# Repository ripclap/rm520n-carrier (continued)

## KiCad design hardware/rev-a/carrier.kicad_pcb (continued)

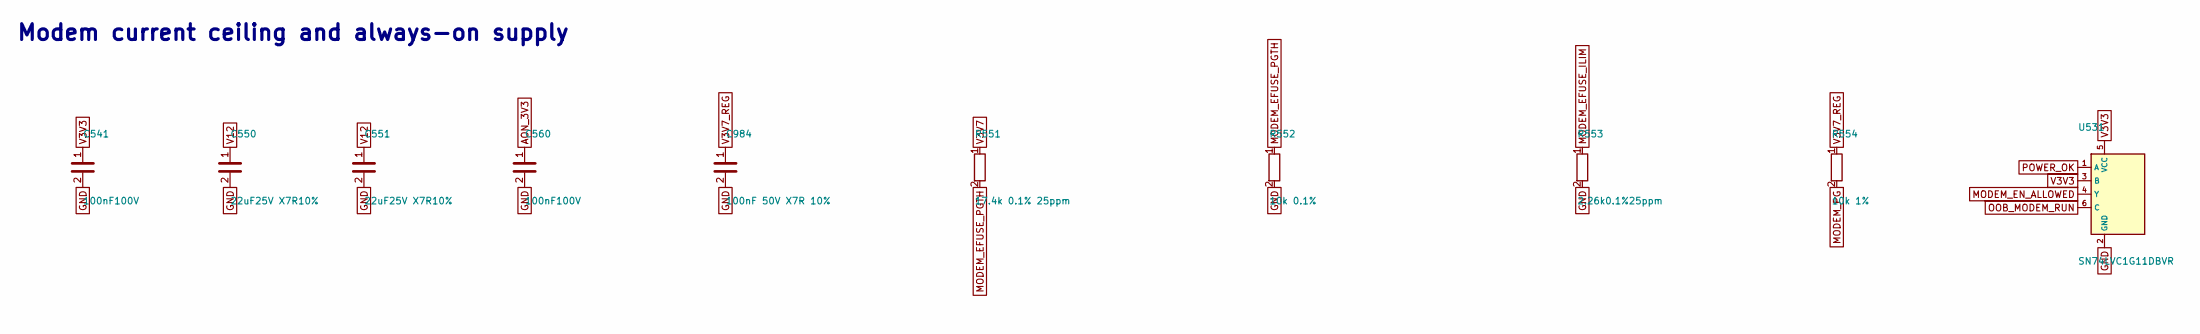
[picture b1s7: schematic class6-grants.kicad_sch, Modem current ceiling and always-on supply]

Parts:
C541, C560: 100nF100V; C_0603_1608Metric; MPN GRM188R72A104KA35D
C550, C551: 22uF25V X7R10%; C_1210_3225Metric; MPN CL32B226KAJNNNE; LCSC C309062
C984: 100nF 50V X7R 10%; C_0402_1005Metric; MPN CL05B104KB5NNNC; LCSC C960916
R551: 17.4k 0.1% 25ppm; R_0402_1005Metric; MPN RT0402BRD0717K4L
R552: 10k 0.1%; R_0402_1005Metric; MPN TNPW040210K0BEED
R553: 2.26k0.1%25ppm; R_0603_1608Metric; MPN RT0603BRD072K26L
R554: 10k 1%; R_0603_1608Metric; MPN RC0603FR-0710KL
U531: SN74LVC1G11DBVR; SOT-23-6; MPN SN74LVC1G11DBVR

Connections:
AON_3V3: C560.1; also elsewhere on the board
GND: C541.2, C550.2, C551.2, C560.2, C984.2, R552.2, R553.2, U531.2 (GND); also elsewhere on the board
MODEM_EFUSE_ILIM: R553.1; also elsewhere on the board
MODEM_EFUSE_PGTH: R551.2, R552.1; also elsewhere on the board
MODEM_EN_ALLOWED: U531.4 (Y); also elsewhere on the board
MODEM_PG: R554.2; also elsewhere on the board
OOB_MODEM_RUN: U531.6 (C); also elsewhere on the board
POWER_OK: U531.1 (A); also elsewhere on the board
V3V3: C541.1, U531.3 (B), U531.5 (VCC); also elsewhere on the board
V3V7: R551.1; also elsewhere on the board
V3V7_REG: C984.1, R554.1; also elsewhere on the board
V12: C550.1, C551.1; also elsewhere on the board

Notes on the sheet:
Modem current ceiling and always-on supply

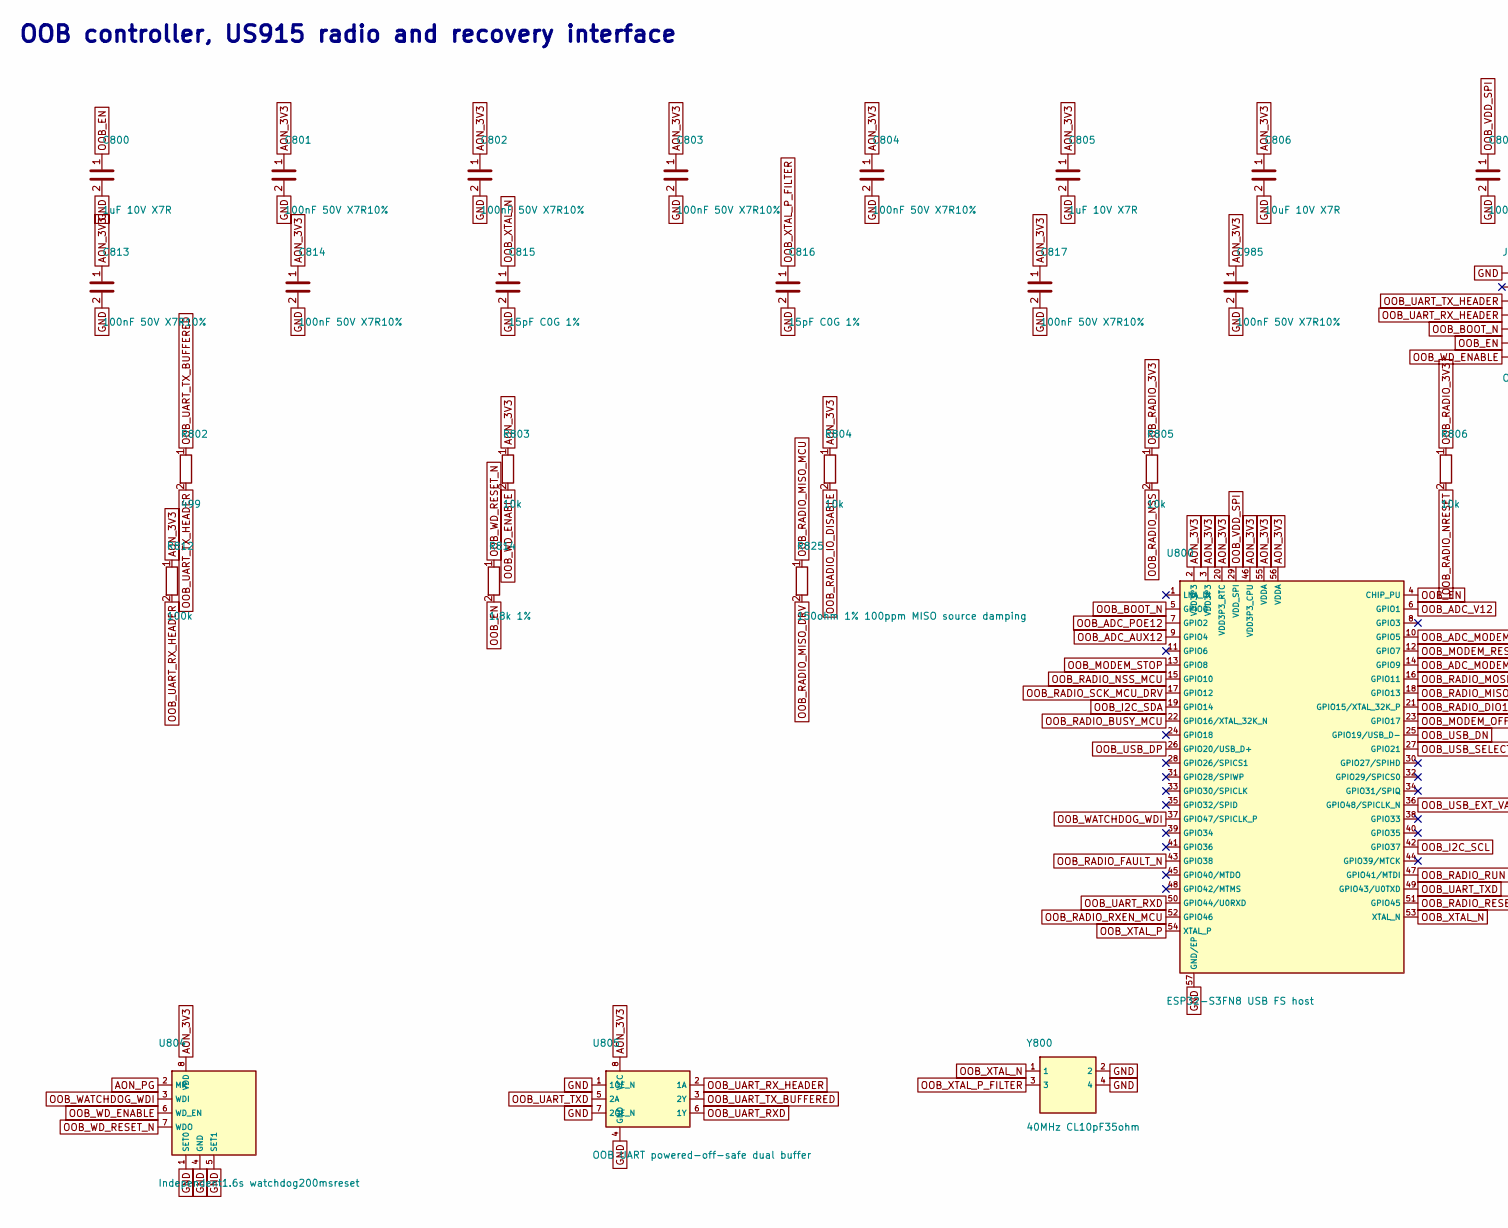
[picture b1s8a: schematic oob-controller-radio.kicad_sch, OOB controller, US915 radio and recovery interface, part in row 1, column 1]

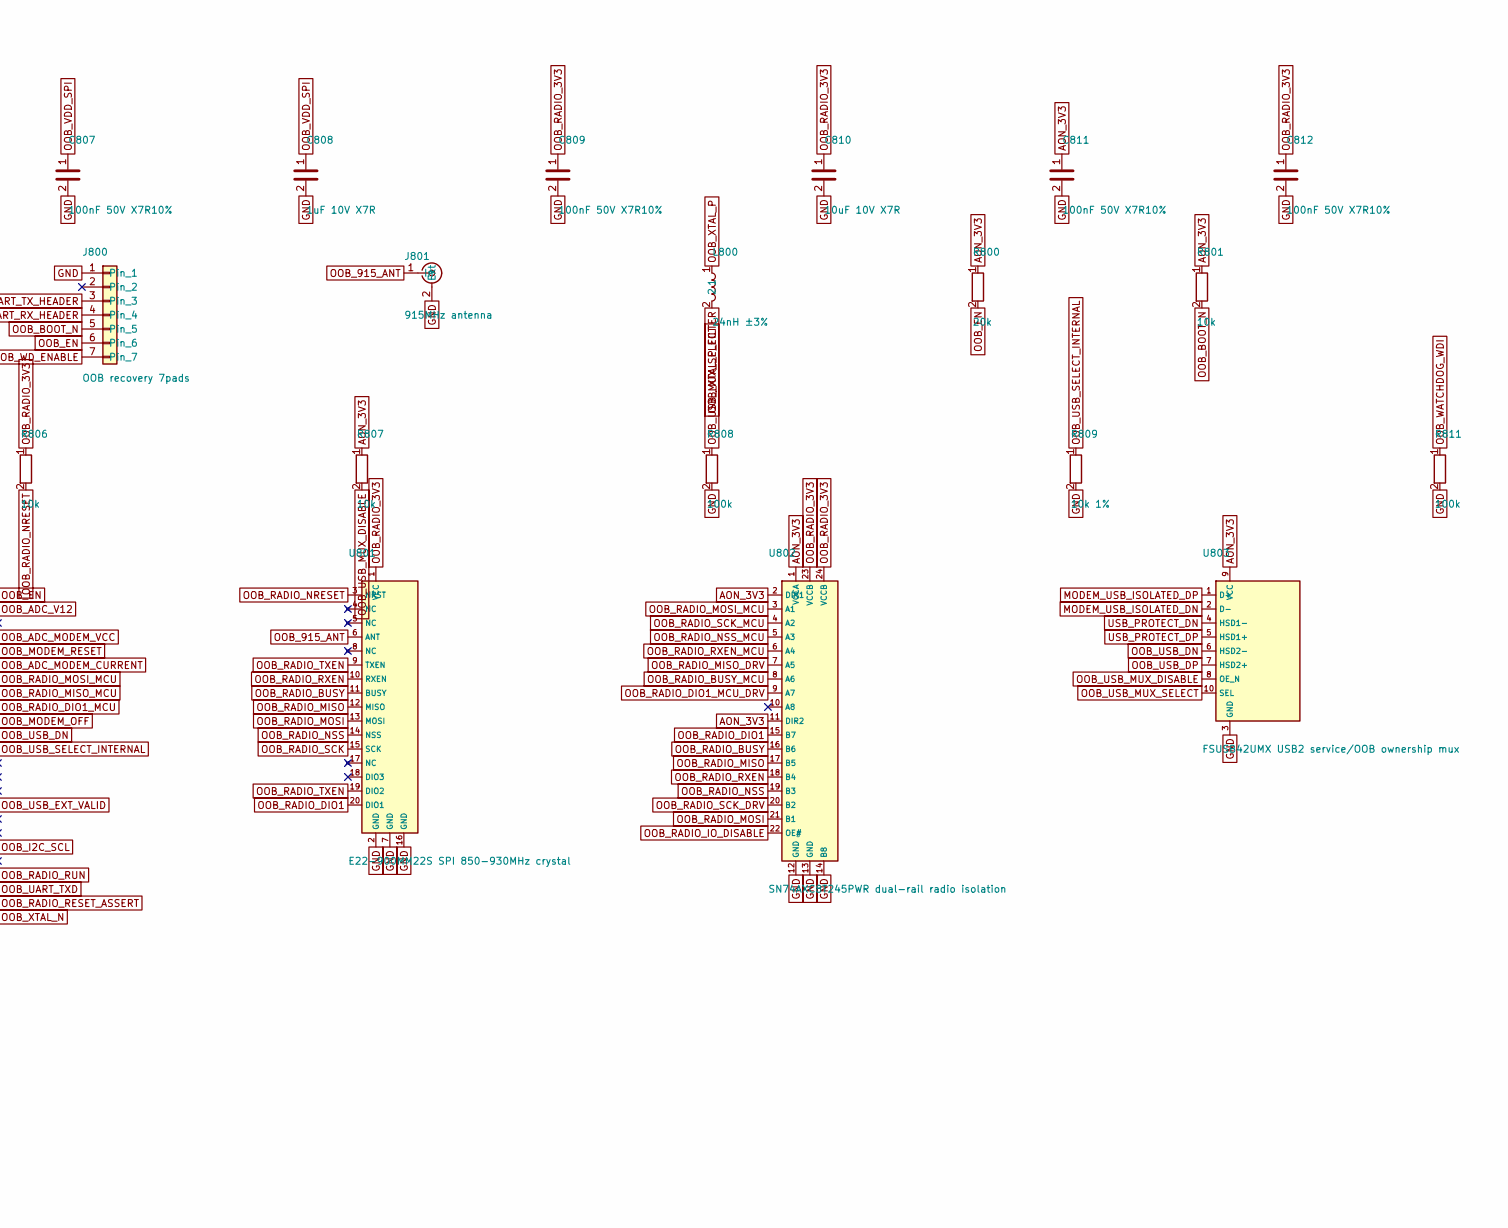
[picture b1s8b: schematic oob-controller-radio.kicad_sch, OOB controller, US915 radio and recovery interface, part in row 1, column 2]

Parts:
C800, C805, C808: 1uF 10V X7R; C_0603_1608Metric; MPN 885012206026
C801, C802, C803, C804, C807, C811, C812, C813, C814, C817, C985: 100nF 50V X7R10%; C_0402_1005Metric; MPN CL05B104KB5NNNC; LCSC C960916
C806, C810: 10uF 10V X7R; C_0805_2012Metric; MPN 885012207026
C809: 100nF 50V X7R10%; C_0402_1005Metric_DenseRevA_C809; MPN CL05B104KB5NNNC; LCSC C960916
C815, C816: 15pF C0G 1%; C_0402_1005Metric; MPN KGM05ACG1H150FH
J800: OOB recovery 7pads; OOB_SERVICE_7PAD; MPN PCB service pads
J801: 915MHz antenna; UFL_HIROSE_DenseRevA_J801; MPN U.FL-R-SMT-1(80)
L800: 24nH ±3%; Murata_LQW15AN_0402_Manufacturer_DenseRevA_L800; MPN LQW15AN24NH00D
R800: 20k; R_0402_1005Metric; MPN CRCW040220K0FKED
R801, R803, R804, R805, R806, R807: 10k; R_0402_1005Metric; MPN CRCW040210K0FKED
R802: 499; R_0402_1005Metric; MPN CRCW0402499RFKED
R808, R811, R812: 100k; R_0402_1005Metric; MPN CRCW0402100KFKED
R809: 10k 1%; R_0402_1005Metric; MPN CRCW040210K0FKED
R814: 1.8k 1%; R_0402_1005Metric; MPN RC0402FR-071K8L; LCSC C163481
R825: 150ohm 1% 100ppm MISO source damping; R_0402_1005Metric; MPN CRCW0402150RFKED
U800: ESP32-S3FN8 USB FS host; ESP32_S3FN8_QFN56; MPN ESP32-S3FN8
U801: E22-900MM22S SPI 850-930MHz crystal; Ebyte_E22_900MM22S_10x10_20Pad_DenseRevA_U801; MPN E22-900MM22S; LCSC C5333985
U802: SN74AXC8T245PWR dual-rail radio isolation; RevA_DensePrimary100_PIN50_Flash_U802; MPN SN74AXC8T245PWR; LCSC C882718
U803: FSUSB42UMX USB2 service/OOB ownership mux; FSUSB42_UQFN10_1p4x1p8; MPN FSUSB42UMX; LCSC C11145
U804: Independent1.6s watchdog200msreset; TI_DDF8_TPS3435; MPN TPS3435CAKAGDDFR; LCSC C6339182
U805: OOB UART powered-off-safe dual buffer; TI_DCU8_LVC2G125; MPN SN74LVC2G125DCUR
Y800: 40MHz CL10pF35ohm; Abracon_ABM8_3225_DenseRevA_Y800; MPN ABM8-40.000MHZ-10-D1G-T; LCSC C1986736

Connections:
AON_3V3: C801.1, C802.1, C803.1, C804.1, C805.1, C806.1, C811.1, C813.1, C814.1, C817.1, C985.1, R800.1, R801.1, R803.1, R804.1, R807.1, R812.1, U800.2 (VDD3P3), U800.3 (VDD3P3), U800.20 (VDD3P3_RTC), U800.46 (VDD3P3_CPU), U800.55 (VDDA), U800.56 (VDDA), U802.1 (VCCA), U802.2 (DIR1), U802.11 (DIR2), U803.9 (VCC), U804.8 (VDD), U805.8 (VCC); also elsewhere on the board
AON_PG: U804.2 (MR); also elsewhere on the board
GND: C800.2, C801.2, C802.2, C803.2, C804.2, C805.2, C806.2, C807.2, C808.2, C809.2, C810.2, C811.2, C812.2, C813.2, C814.2, C815.2, C816.2, C817.2, C985.2, J800.1, J801.2 (Ext), R808.2, R809.2, R811.2, U800.57 (GND/EP), U801.2 (GND), U801.7 (GND), U801.16 (GND), U802.12 (GND), U802.13 (GND), U802.14 (B8), U803.3 (GND), U804.1 (SET0), U804.4 (GND), U804.5 (SET1), U805.1 (1OE_N), U805.4 (GND), U805.7 (2OE_N), Y800.2, Y800.4; also elsewhere on the board
MODEM_USB_ISOLATED_DN: U803.2 (D-); also elsewhere on the board
MODEM_USB_ISOLATED_DP: U803.1 (D+); also elsewhere on the board
OOB_915_ANT: J801.1 (In), U801.6 (ANT)
OOB_ADC_AUX12: U800.9 (GPIO4); also elsewhere on the board
OOB_ADC_MODEM_CURRENT: U800.14 (GPIO9); also elsewhere on the board
OOB_ADC_MODEM_VCC: U800.10 (GPIO5); also elsewhere on the board
OOB_ADC_POE12: U800.7 (GPIO2); also elsewhere on the board
OOB_ADC_V12: U800.6 (GPIO1); also elsewhere on the board
OOB_BOOT_N: J800.5, R801.2, U800.5 (GPIO0)
OOB_EN: C800.1, J800.6, R800.2, R814.2, U800.4 (CHIP_PU); also elsewhere on the board
OOB_I2C_SCL: U800.42 (GPIO37); also elsewhere on the board
OOB_I2C_SDA: U800.19 (GPIO14); also elsewhere on the board
OOB_MODEM_OFF: U800.23 (GPIO17); also elsewhere on the board
OOB_MODEM_RESET: U800.12 (GPIO7); also elsewhere on the board
OOB_MODEM_STOP: U800.13 (GPIO8); also elsewhere on the board
OOB_RADIO_3V3: C809.1, C810.1, C812.1, R805.1, R806.1, U801.1 (VCC), U802.23 (VCCB), U802.24 (VCCB); also elsewhere on the board
OOB_RADIO_BUSY: U801.11 (BUSY), U802.16 (B6)
OOB_RADIO_BUSY_MCU: U800.22 (GPIO16/XTAL_32K_N), U802.8 (A6)
OOB_RADIO_DIO1: U801.20 (DIO1), U802.15 (B7)
OOB_RADIO_DIO1_MCU: U800.21 (GPIO15/XTAL_32K_P); also elsewhere on the board
OOB_RADIO_DIO1_MCU_DRV: U802.9 (A7); also elsewhere on the board
OOB_RADIO_FAULT_N: U800.43 (GPIO38); also elsewhere on the board
OOB_RADIO_IO_DISABLE: R804.2, U802.22 (OE#); also elsewhere on the board
OOB_RADIO_MISO: U801.12 (MISO), U802.17 (B5)
OOB_RADIO_MISO_DRV: R825.2, U802.7 (A5)
OOB_RADIO_MISO_MCU: R825.1, U800.18 (GPIO13)
OOB_RADIO_MOSI: U801.13 (MOSI), U802.21 (B1)
OOB_RADIO_MOSI_MCU: U800.16 (GPIO11), U802.3 (A1)
OOB_RADIO_NRESET: R806.2, U801.3 (NRST); also elsewhere on the board
OOB_RADIO_NSS: R805.2, U801.14 (NSS), U802.19 (B3)
OOB_RADIO_NSS_MCU: U800.15 (GPIO10), U802.5 (A3)
OOB_RADIO_RESET_ASSERT: U800.51 (GPIO45); also elsewhere on the board
OOB_RADIO_RUN: U800.47 (GPIO41/MTDI); also elsewhere on the board
OOB_RADIO_RXEN: U801.10 (RXEN), U802.18 (B4)
OOB_RADIO_RXEN_MCU: U800.52 (GPIO46), U802.6 (A4); also elsewhere on the board
OOB_RADIO_SCK: U801.15 (SCK); also elsewhere on the board
OOB_RADIO_SCK_DRV: U802.20 (B2); also elsewhere on the board
OOB_RADIO_SCK_MCU: U802.4 (A2); also elsewhere on the board
OOB_RADIO_SCK_MCU_DRV: U800.17 (GPIO12); also elsewhere on the board
OOB_RADIO_TXEN: U801.9 (TXEN), U801.19 (DIO2)
OOB_UART_RXD: U800.50 (GPIO44/U0RXD), U805.6 (1Y)
OOB_UART_RX_HEADER: J800.4, R812.2, U805.2 (1A)
OOB_UART_TXD: U800.49 (GPIO43/U0TXD), U805.5 (2A)
OOB_UART_TX_BUFFERED: R802.1, U805.3 (2Y)
OOB_UART_TX_HEADER: J800.3, R802.2
OOB_USB_DN: U800.25 (GPIO19/USB_D-), U803.6 (HSD2-)
OOB_USB_DP: U800.26 (GPIO20/USB_D+), U803.7 (HSD2+)
OOB_USB_EXT_VALID: U800.36 (GPIO48/SPICLK_N); also elsewhere on the board
OOB_USB_MUX_DISABLE: R807.2, U803.8 (OE_N); also elsewhere on the board
OOB_USB_MUX_SELECT: R808.1, U803.10 (SEL); also elsewhere on the board
OOB_USB_SELECT_INTERNAL: R809.1, U800.27 (GPIO21); also elsewhere on the board
OOB_VDD_SPI: C807.1, C808.1, U800.29 (VDD_SPI)
OOB_WATCHDOG_WDI: R811.1, U800.37 (GPIO47/SPICLK_P), U804.3 (WDI)
OOB_WD_ENABLE: J800.7, R803.2, U804.6 (WD_EN)
OOB_WD_RESET_N: R814.1, U804.7 (WDO)
OOB_XTAL_N: C815.1, U800.53 (XTAL_N), Y800.1
OOB_XTAL_P: L800.1, U800.54 (XTAL_P)
OOB_XTAL_P_FILTER: C816.1, L800.2, Y800.3
USB_PROTECT_DN: U803.4 (HSD1-); also elsewhere on the board
USB_PROTECT_DP: U803.5 (HSD1+); also elsewhere on the board

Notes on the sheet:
OOB controller, US915 radio and recovery interface

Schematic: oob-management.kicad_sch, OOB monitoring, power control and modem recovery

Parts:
C552: 100nF50V X7R10%; C_0402_1005Metric; MPN CL05B104KB5NNNC; LCSC C960916
C553, C554, C555, C561: 22uF25V X7R10%; C_1210_3225Metric; MPN CL32B226KAJNNNE; LCSC C309062
C558: 10uF10V; C_0805_2012Metric; MPN 885012207026
C563: 2.2nF 25V; C_0402_1005Metric; MPN GRM155R71E222KA01D
C741, C742, C745, C746, C747, C750, C751, C753, C760, C761, C762, C763, C840, C902, C903, C906, C908: 100nF 50V X7R10%; C_0402_1005Metric; MPN CL05B104KB5NNNC; LCSC C960916
L520: 2.2uH5.5A; L_Bourns_SRP5030T; MPN SRP5030TA-2R2M
Q740, Q742: NX3008NBK,215; SOT-23; MPN NX3008NBK,215
Q746: NX3008NBK,215; SOT-23_DenseRevA_Q746; MPN NX3008NBK,215
R560: 18.2k 1%; R_0603_1608Metric; MPN RC0603FR-0718K2L
R561: 32.4k0.1%25ppm; R_0603_1608Metric; MPN RT0603BRD0732K4L; LCSC C861323
R562: 10k0.1%25ppm; R_0603_1608Metric; MPN RT0603BRD0710KL
R563, R573: 10k 1%; R_0603_1608Metric; MPN RC0603FR-0710KL
R564: 10k 0.1% 25ppm; R_0402_1005Metric; MPN TNPW040210K0BEED
R565, R755: 10k 1%; R_0402_1005Metric; MPN CRCW040210K0FKED
R566, R752: 10k; R_0402_1005Metric; MPN CRCW040210K0FKED
R572: 76.8k0.1%25ppm; R_0402_1005Metric; MPN RT0402BRD0776K8L; LCSC C852913
R740, R744, R783, R840, R841: 1k; R_0402_1005Metric; MPN CRCW04021K00FKED
R741, R745: 10k1%; R_0402_1005Metric; MPN CRCW040210K0FKED
R746, R750, R757, R777, R778: 100k; R_0402_1005Metric; MPN CRCW0402100KFKED
R747: 953ohm0.1%25ppm; RevA_Dense100_50_R747; MPN RT0603BRD07953RL
R754: 82.5k0.1%25ppm; R_0402_1005Metric; MPN RT0402BRD0782K5L
R756: 1M 1%; R_0402_1005Metric; MPN CRCW04021M00FKED
R760, R762, R764: 100k; R_0402_1005Metric; MPN TNPW0402100KBEED
R761, R763, R765, R781, R782: 10k; R_0402_1005Metric; MPN TNPW040210K0BEED
R766, R780: 1k 1% 100ppm; R_0402_1005Metric; MPN CRCW04021K00FKED
R767: 100ohm 1% 100ppm; R_0402_1005Metric; MPN CRCW0402100RFKED
R768: 27k 0.1% 25ppm; RevA_Dense100_50_R768; MPN RT0603BRD0727KL
R769: 10k; RevA_Dense100_50_R769; MPN TNPW040210K0BEED
R775, R776: 2.49k 1% 0402; R_0402_1005Metric; MPN CRCW04022K49FKED
R779: 1k 1% 100ppm; RevA_Dense100_50_R779; MPN CRCW04021K00FKED
R784: 10k1%; R_0402_1005Metric_DenseRevA_R784; MPN CRCW040210K0FKED
U520: TPS62912RPUR; TI_RPU0010A_TPS62912; MPN TPS62912RPUR
U522: SN74LVC1G11DBVR; SOT-23-6; MPN SN74LVC1G11DBVR
U523: TPS2553DBVR-1 latched radio power; SOT-23-6; MPN TPS2553DBVR-1; LCSC C111738
U742: SN74LVC1G00DBVR radio OE guard; SOT-23-5; MPN SN74LVC1G00DBVR
U748: TMUX1511PWR; TSSOP-14_4.4x5mm_P0.65mm; MPN TMUX1511PWR
U749: SN74LVC3G17DCUR; TI_DCU8_LVC3G17; MPN SN74LVC3G17DCUR
U752: TMP102AIDRLR; SOT563_TMP102; MPN TMP102AIDRLR
U756: TPS3808G33DBVR radio PG; SOT-23-6; MPN TPS3808G33DBVR; LCSC C43698
U840: NCA9536DQJ I2C status; Nexperia_SOT505_3_Primary; MPN NCA9536DQJ

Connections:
AON_3V3: C553.1, C554.1, C555.1, C561.1, C742.1, C745.1, C746.1, C747.1, C750.1, C751.1, C753.1, C840.1, C902.1, C903.1, C906.1, C908.1, L520.2, R561.1, R563.1, R573.1, R750.1, R775.1, R776.1, R781.1, U520.3 (VO), U522.5 (VCC), U522.6 (C), U523.1 (IN), U742.5 (VCC), U748.14 (VDD), U749.8 (VCC), U752.5 (V+), U756.3 (MR#), U756.6 (VDD), U840.8 (VCC); also elsewhere on the board
AON_PG: R563.2, U520.5 (PG), U522.1 (A), U748.1 (SEL1), U748.4 (SEL2), U748.10 (SEL3), U748.13 (SEL4); also elsewhere on the board
GND: C552.2, C553.2, C554.2, C555.2, C558.2, C561.2, C563.2, C741.2, C742.2, C745.2, C746.2, C747.2, C750.2, C751.2, C753.2, C760.2, C761.2, C762.2, C763.2, C840.2, C902.2, C903.2, C906.2, C908.2, Q740.2 (S), Q742.2 (S), Q746.2 (S), R560.2, R562.2, R564.2, R565.2, R566.2, R572.2, R741.2, R745.2, R746.2, R747.2, R755.2, R757.2, R761.2, R763.2, R765.2, R767.2, R769.2, R777.2, R778.2, R779.2, R780.2, R782.2, R783.2, R784.2, U520.4 (PGND), U520.7 (PSNS), U522.2 (GND), U523.2 (GND), U742.3 (GND), U748.7 (GND), U749.4 (GND), U749.6 (3A), U752.2 (GND), U752.4 (ADD0), U756.2 (GND), U840.4 (GND); also elsewhere on the board
MODEM_EFUSE_DVDT_RC: C741.1; also elsewhere on the board
MODEM_EFUSE_ILIM: R747.1, R756.1; also elsewhere on the board
MODEM_EFUSE_OVP: R769.1; also elsewhere on the board
MODEM_EFUSE_OVP_TOP: R768.2; also elsewhere on the board
MODEM_ENABLE_MR: Q742.3 (D); also elsewhere on the board
MODEM_EN_ALLOWED: R755.1; also elsewhere on the board
MODEM_IMON_TO_ISOLATOR: R756.2; also elsewhere on the board
MODEM_PG: R778.1, U749.3 (2A); also elsewhere on the board
OOB_ADC_AUX12: U748.9 (S3); also elsewhere on the board
OOB_ADC_MODEM_CURRENT: R757.1; also elsewhere on the board
OOB_ADC_MODEM_VCC: U748.12 (S4); also elsewhere on the board
OOB_ADC_POE12: U748.6 (D2); also elsewhere on the board
OOB_ADC_V12: U748.3 (D1); also elsewhere on the board
OOB_AON_EN: R564.1, R754.2, U520.1 (EN_SYNC)
OOB_AUX12_SCALED: C762.1, R764.2, R765.1, U748.8 (D3)
OOB_FB: R561.2, R562.1, U520.9 (FB)
OOB_I2C_SCL: R776.2, U752.1 (SCL), U840.6 (SCL); also elsewhere on the board
OOB_I2C_SDA: R775.2, U752.6 (SDA), U840.7 (SDA); also elsewhere on the board
OOB_MAIN_OK: R840.1, U749.7 (1Y)
OOB_MODEM_OFF: R740.1; also elsewhere on the board
OOB_MODEM_PG: R841.1, U749.5 (2Y)
OOB_MODEM_RESET: R746.1; also elsewhere on the board
OOB_MODEM_RUN: Q740.3 (D), R752.2; also elsewhere on the board
OOB_MODEM_STOP: R744.1; also elsewhere on the board
OOB_MODEM_VCC_SCALED: C763.1, R766.2, R767.1, U748.11 (D4)
OOB_MON_MAIN_IN: R840.2, U840.1 (P0)
OOB_MON_MODEM_PG_IN: R841.2, U840.2 (P1)
OOB_NRSS: C552.1, U520.8 (NR_SS)
OOB_POE12_SCALED: C761.1, R762.2, R763.1, U748.5 (S2)
OOB_QUAL_REF: R781.2, R782.1; also elsewhere on the board
OOB_RADIO_3V3: C558.1, R783.1, U523.6 (OUT), U756.5 (SENSE); also elsewhere on the board
OOB_RADIO_FAULT_N: R750.2, U523.4 (FAULT#); also elsewhere on the board
OOB_RADIO_ILM: R572.1, U523.5 (ILIM)
OOB_RADIO_IO_DISABLE: U742.4 (Y); also elsewhere on the board
OOB_RADIO_NRESET: Q746.3 (D); also elsewhere on the board
OOB_RADIO_POWER_GOOD: R573.2, U742.2 (B), U756.1 (RESET#)
OOB_RADIO_RESET_ASSERT: Q746.1 (G), R784.1; also elsewhere on the board
OOB_RADIO_RUN: R565.1, U522.3 (B); also elsewhere on the board
OOB_RADIO_RUN_ALLOWED: U522.4 (Y), U523.3 (EN), U742.1 (A)
OOB_RADIO_RXEN_MCU: R566.1; also elsewhere on the board
OOB_SCONF: R560.1, U520.10 (S_CONF)
OOB_SW: L520.1, U520.2 (SW)
OOB_V12_SCALED: C760.1, R760.2, R761.1, U748.2 (S1)
POWER_OK: R777.1, U749.1 (1A); also elsewhere on the board
Q740_G: Q740.1 (G), R740.2, R741.1
Q742_G: Q742.1 (G), R744.2, R745.1
V3V3: R752.1; also elsewhere on the board
V3V7: R766.1, R780.1; also elsewhere on the board
V3V7_REG: R768.1, R779.1; also elsewhere on the board
V12: C563.1, R754.1, R760.1, U520.6 (VIN); also elsewhere on the board
V12_PD: R762.1; also elsewhere on the board
VDC_IN: R764.1; also elsewhere on the board

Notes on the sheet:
OOB monitoring, power control and modem recovery

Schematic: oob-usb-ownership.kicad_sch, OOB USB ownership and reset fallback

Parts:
U770: SN74LVC1G04DBVR; SOT-23-5; MPN SN74LVC1G04DBVR
U771: USB priority three-input AND; SOT-23-6; MPN SN74LVC1G11DBVR
U774: NAND2 USB mux disable; SOT-23-5; MPN SN74LVC1G00DBVR; LCSC C7826
U776: SN74LVC1G32DBVR; SOT-23-5; MPN SN74LVC1G32DBVR

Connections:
AON_3V3: U770.5 (VCC), U771.5 (VCC), U774.5 (VCC), U776.5 (VCC); also elsewhere on the board
AON_PG: U774.1 (A); also elsewhere on the board
GND: U770.3 (GND), U771.2 (GND), U774.3 (GND), U776.3 (GND); also elsewhere on the board
OOB_EN: U771.3 (B); also elsewhere on the board
OOB_USB_EXT_ABSENT: U770.4 (Y), U771.6 (C)
OOB_USB_EXT_VALID: U770.2 (A), U776.1 (A); also elsewhere on the board
OOB_USB_MUX_DISABLE: U774.4 (Y); also elsewhere on the board
OOB_USB_MUX_SELECT: U771.4 (Y), U776.2 (B); also elsewhere on the board
OOB_USB_SELECT_INTERNAL: U771.1 (A); also elsewhere on the board
OOB_USB_SESSION_VALID: U774.2 (B), U776.4 (Y); also elsewhere on the board

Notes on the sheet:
OOB USB ownership and reset fallback

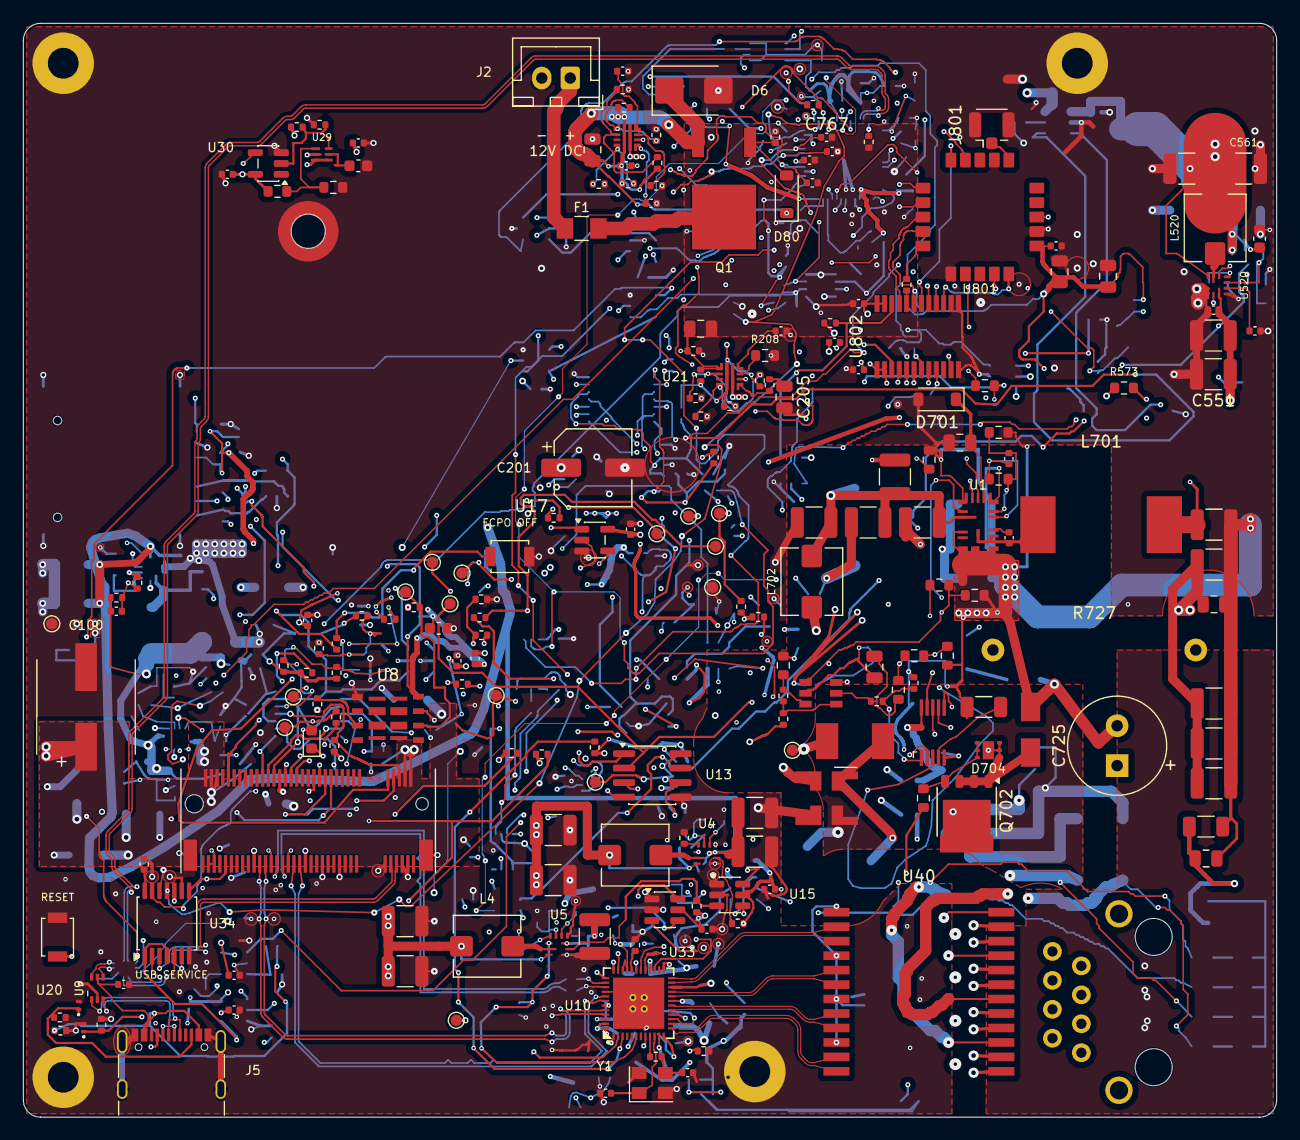
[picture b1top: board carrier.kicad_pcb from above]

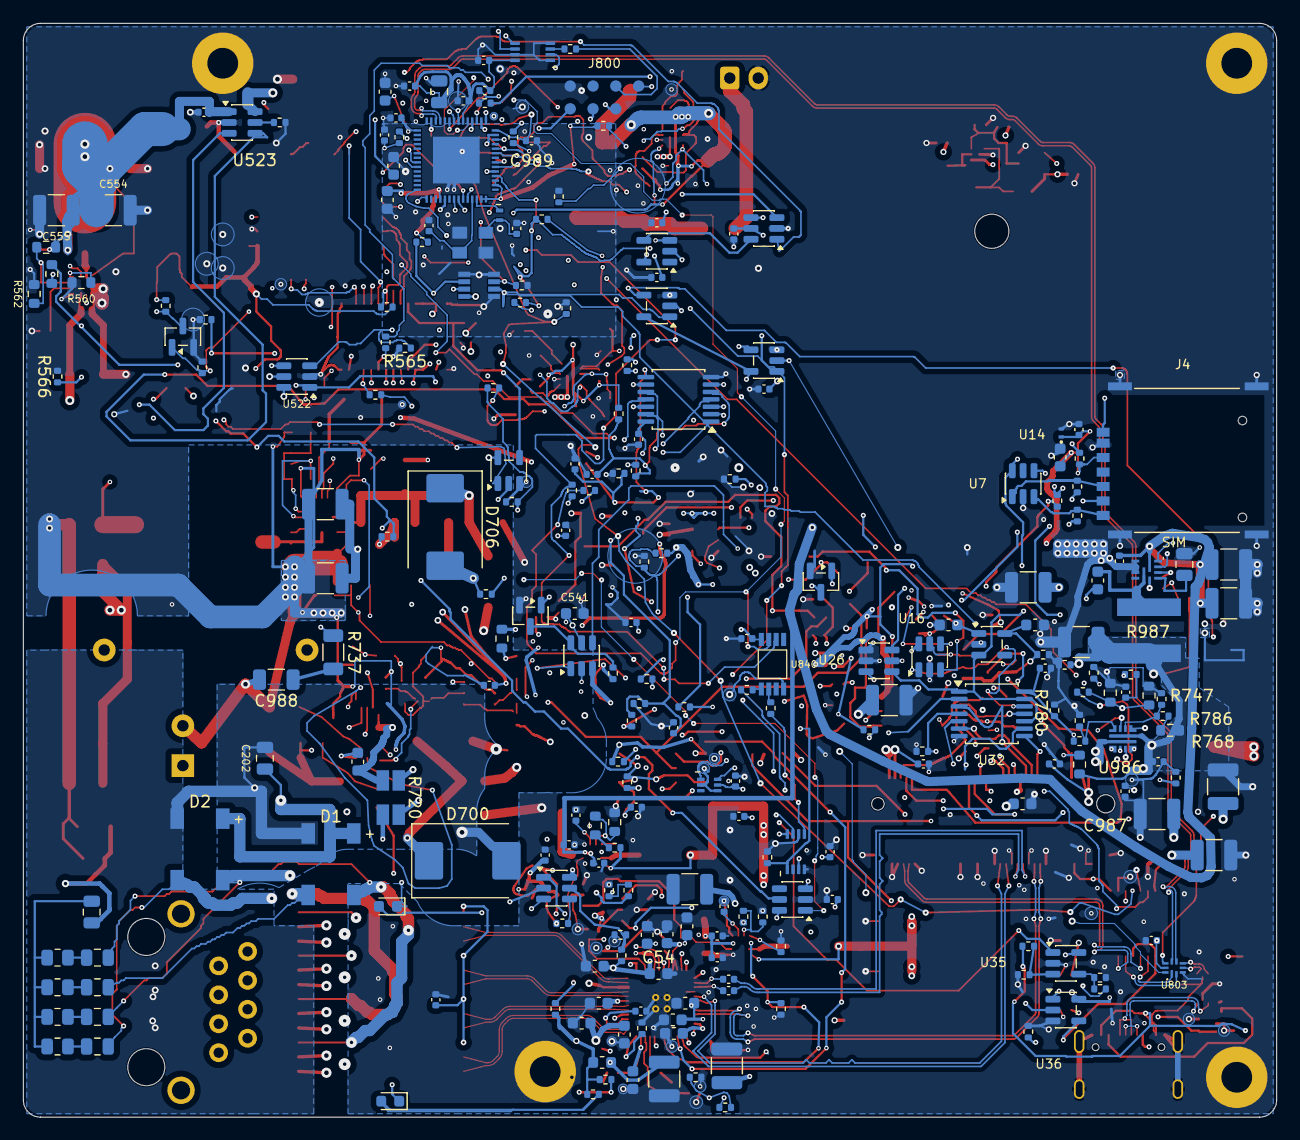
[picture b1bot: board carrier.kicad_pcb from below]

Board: 6 copper layers, 110.0 x 96.0 mm, 444 parts (234 on the bottom side), 269 nets.
